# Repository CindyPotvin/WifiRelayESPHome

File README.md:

# Wifi Relay board to use with ESPHome

An ESP8266 board with a pair of relay for use with Home Assistant and ESPHome.

Parts list is in the parts.txt file.

Check out the following post for more details: https://robotsbench.com/controlling-relays-with-home-assistant-and-esphome/

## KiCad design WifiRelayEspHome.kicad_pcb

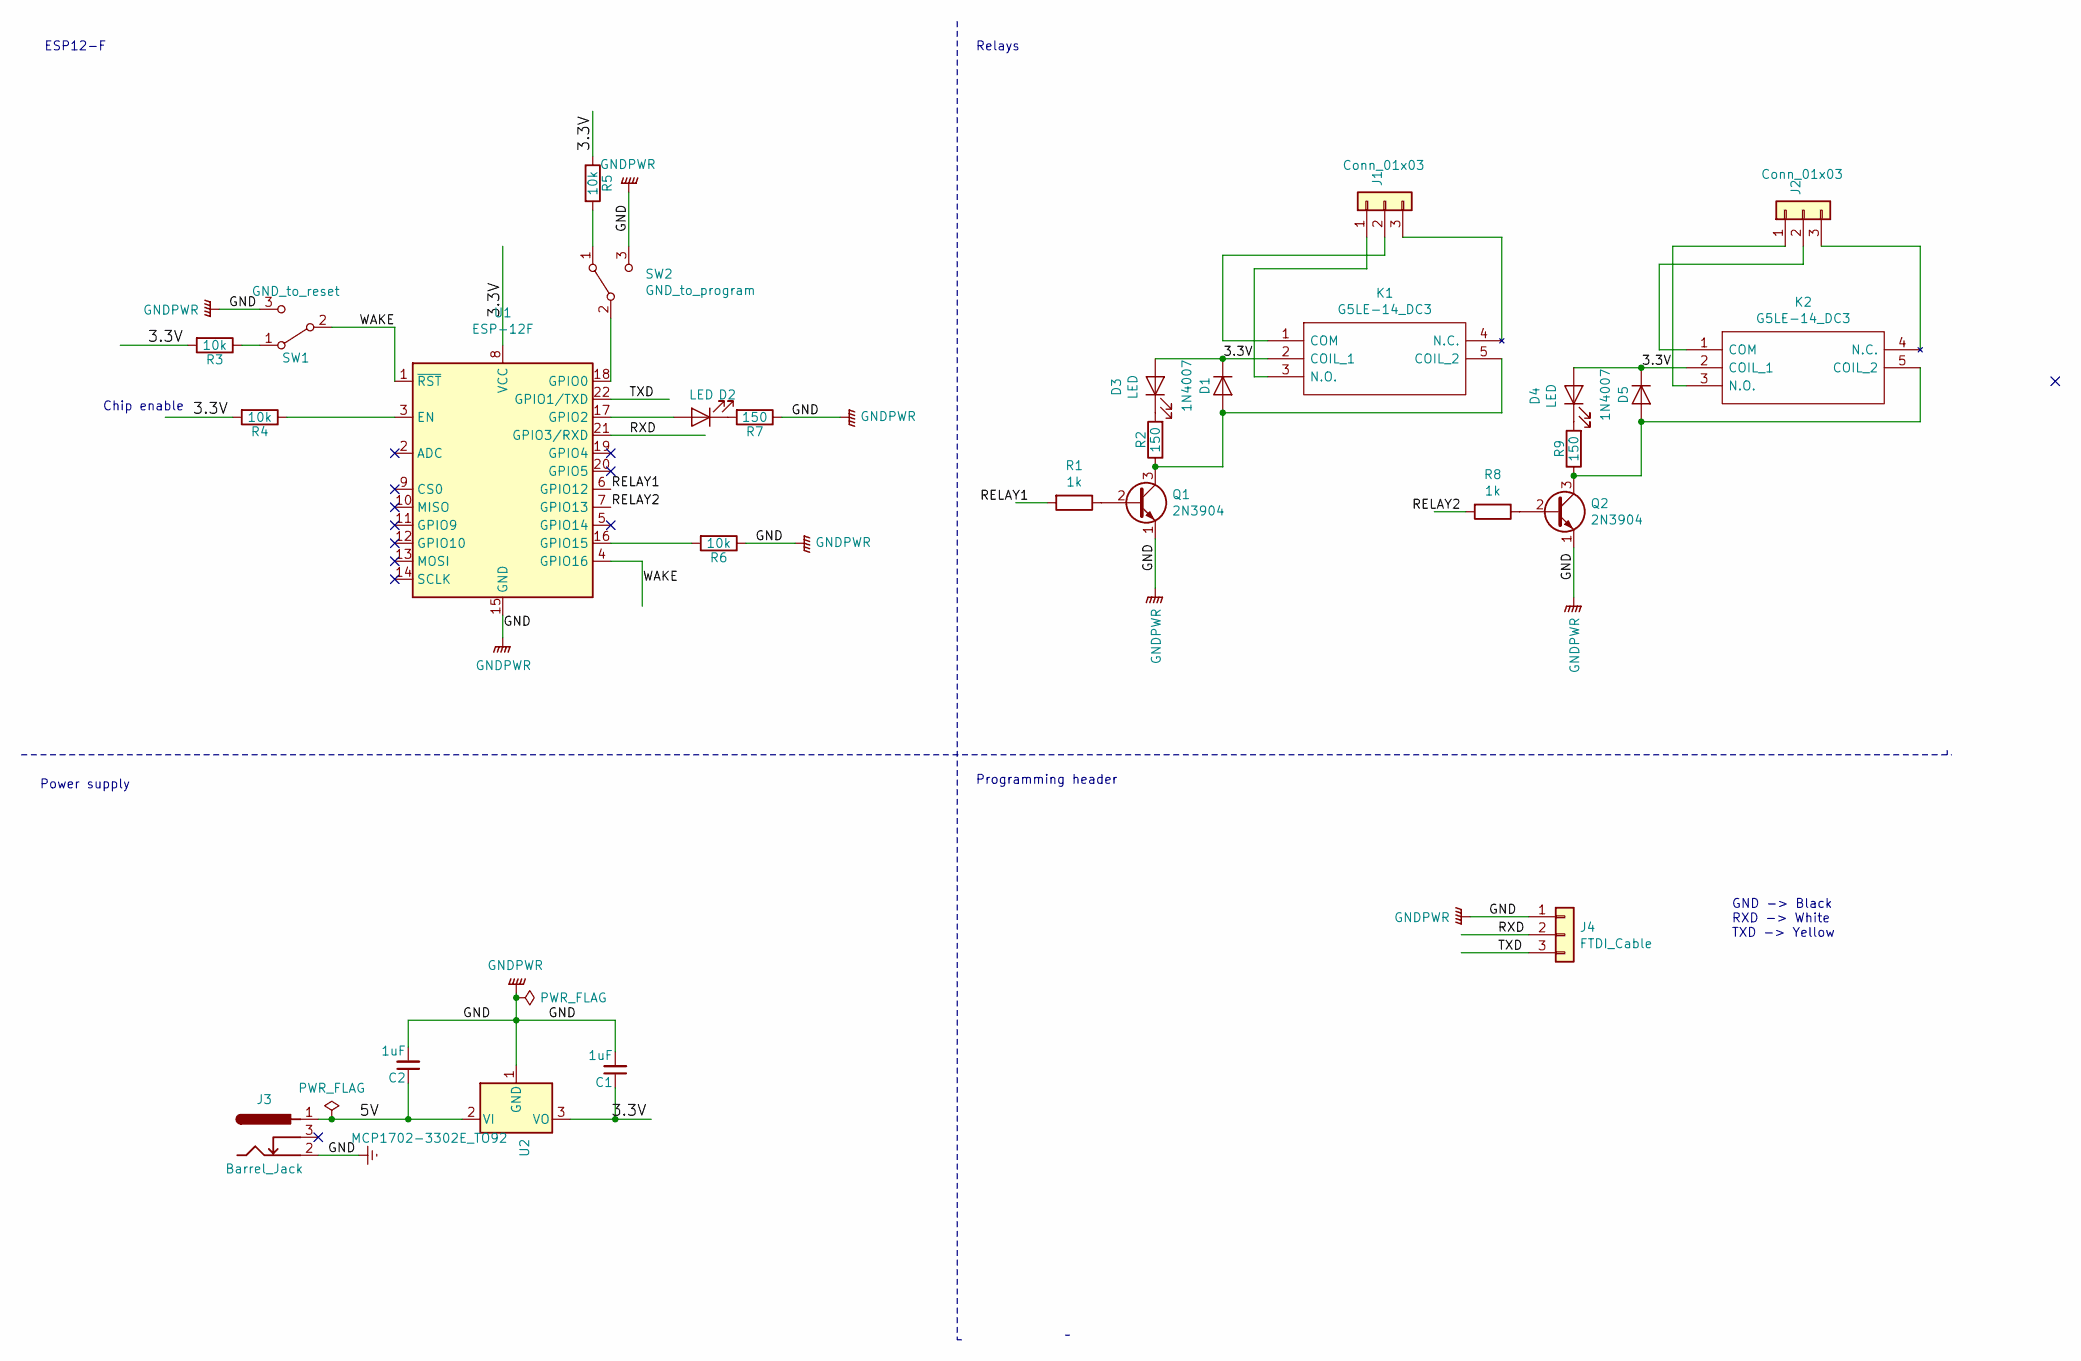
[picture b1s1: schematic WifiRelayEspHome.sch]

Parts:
C1, C2: 1uF; FG18X7R1H334KRT00
D1, D5: 1N4007; D_DO-35_SOD27_P7.62mm_Horizontal
D2, D3, D4: LED; LED_D5.0mm
J1, J2: Conn_01x03; SHDR3W100P0X500_1X3_1500X760X1000P
J3: Barrel_Jack; PJ-102AH
J4: FTDI_Cable; PinHeader_1x03_P2.54mm_Vertical
K1, K2: G5LE-14_DC3; G5LE-14_SPDT; Mouser Part Number 653-G5LE-14DC3
Q1, Q2: 2N3904; TO-92_Inline
R1, R8: 1k; R_Axial_DIN0207_L6.3mm_D2.5mm_P2.54mm_Vertical
R2, R7, R9: 150; R_Axial_DIN0204_L3.6mm_D1.6mm_P2.54mm_Vertical
R3, R4, R5, R6: 10k; R_Axial_DIN0207_L6.3mm_D2.5mm_P2.54mm_Vertical
SW1: GND_to_reset; B3F-1000
SW2: GND_to_program; EG1218
U1: ESP-12F; ESP-12E
U2: MCP1702-3302E_TO92; TO-92_Inline

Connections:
/3.3V: C1.1, D1.1 (K), D3.2 (A), D4.2 (A), D5.1 (K), K1.2 (COIL_1), K2.2 (COIL_1), R3.2, R4.2, R5.1, U1.8 (VCC), U2.3 (VO)
/5V: C2.1, J3.1, U2.2 (VI)
/RELAY1: R1.2, U1.6 (GPIO12)
/RELAY2: R8.2, U1.7 (GPIO13)
/RXD: J4.2, U1.21 (GPIO3/RXD)
/TXD: J4.3, U1.22 (GPIO1/TXD)
/WAKE: SW1.2 (B), U1.1 (~RST), U1.4 (GPIO16)
Earth: C1.2, C2.2, J3.2, J4.1, Q1.1 (E), Q2.1 (E), R6.1, R7.1, SW1.3 (C), SW2.3 (C), U1.15 (GND), U2.1 (GND)
unnamed: D1.2 (A), K1.5 (COIL_2), Q1.3 (C), R2.1
unnamed: D2.1 (K), R7.2
unnamed: D2.2 (A), U1.17 (GPIO2)
unnamed: D3.1 (K), R2.2
unnamed: D4.1 (K), R9.2
unnamed: D5.2 (A), K2.5 (COIL_2), Q2.3 (C), R9.1
unnamed: J1.1, K1.3 (N.O.)
unnamed: J1.2, K1.1 (COM)
unnamed: J1.3, K1.4 (N.C.)
unnamed: J2.1, K2.3 (N.O.)
unnamed: J2.2, K2.1 (COM)
unnamed: J2.3, K2.4 (N.C.)
unnamed: Q1.2 (B), R1.1
unnamed: Q2.2 (B), R8.1
unnamed: R3.1, SW1.1 (A)
unnamed: R4.1, U1.3 (EN)
unnamed: R5.2, SW2.1 (A)
unnamed: R6.2, U1.16 (GPIO15)
unnamed: SW2.2 (B), U1.18 (GPIO0)

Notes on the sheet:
Chip enable
GND -> Black RXD -> White TXD -> Yellow
ESP12-F
Power supply
Programming header
Relays

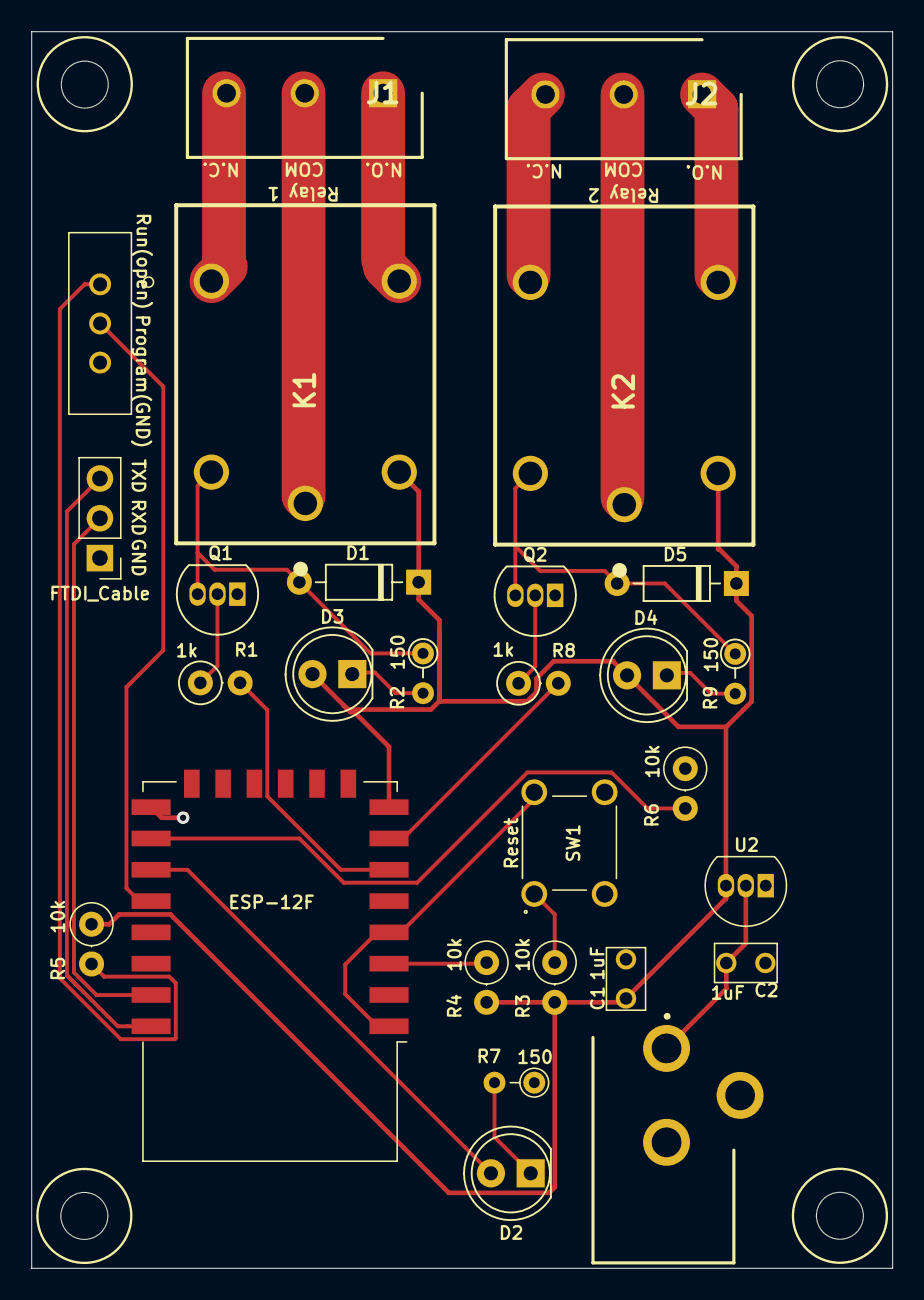
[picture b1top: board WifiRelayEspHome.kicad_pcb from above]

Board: 2 copper layers, 55.0 x 79.0 mm, 28 parts (0 on the bottom side), 27 nets.

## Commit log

2022-03-06 First commit, before sending to fabrication
2022-03-07 Added github link to silkscren
2023-04-10 Final version after testing: changed pins, moved barrel jack and added mounting holes
